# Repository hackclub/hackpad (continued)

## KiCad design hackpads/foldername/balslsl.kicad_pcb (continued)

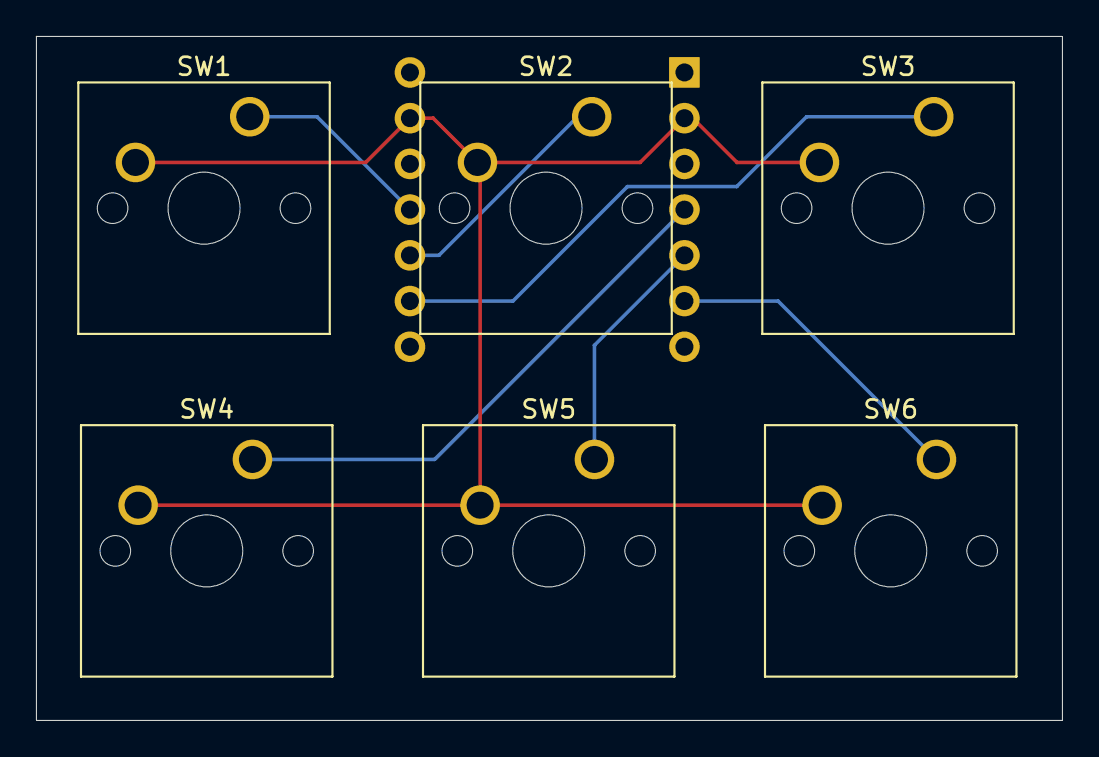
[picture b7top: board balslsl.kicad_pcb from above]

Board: 2 copper layers, 57.0 x 38.0 mm, 7 parts (1 on the bottom side), 7 nets.

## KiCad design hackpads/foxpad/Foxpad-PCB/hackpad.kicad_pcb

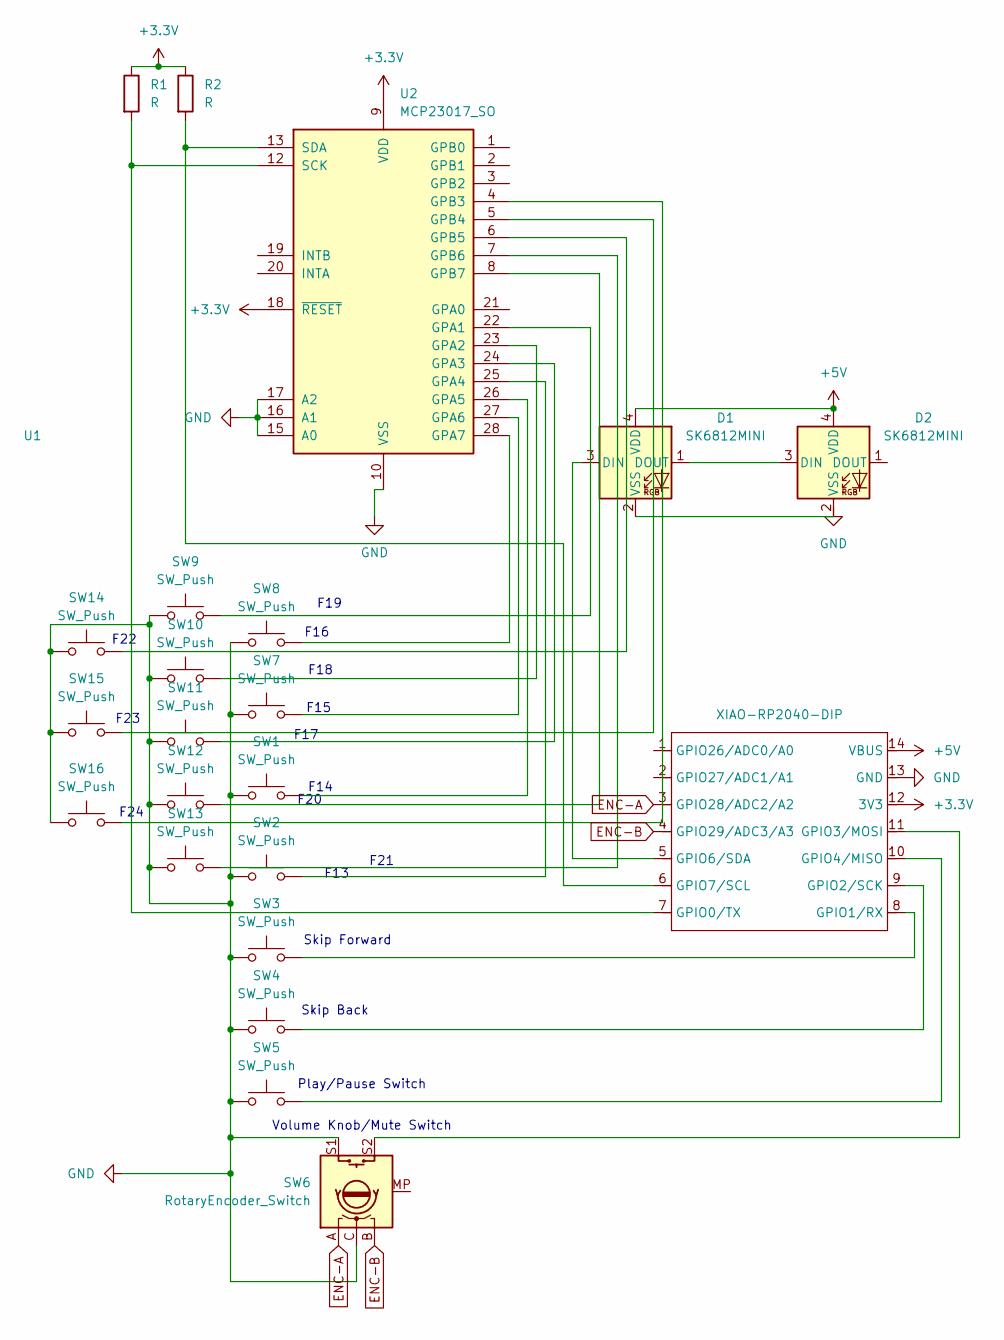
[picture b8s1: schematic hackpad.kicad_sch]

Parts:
D1, D2: SK6812MINI; LED_SK6812MINI_PLCC4_3.5x3.5mm_P1.75mm
R1, R2: R; R_Axial_DIN0204_L3.6mm_D1.6mm_P7.62mm_Horizontal
SW1, SW2, SW3, SW4, SW5, SW7, SW8, SW9, SW10, SW11, SW12, SW13, SW14, SW15, SW16: SW_Push; SW_Cherry_MX_1.00u_PCB
SW6: RotaryEncoder_Switch; RotaryEncoder_Alps_EC11E-Switch_Vertical_H20mm_CircularMoun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
U1: XIAO-RP2040-DIP
U2: MCP23017_SO; SOIC-28W_7.5x17.9mm_P1.27mm

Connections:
+3.3V: R1.1, R2.1, U1.12 (3V3), U2.9 (VDD), U2.18 (~RESET)
+5V: D1.4 (VDD), D2.4 (VDD), U1.14 (VBUS)
ENC-A: SW6.A, U1.3 (GPIO28/ADC2/A2)
ENC-B: SW6.B, U1.4 (GPIO29/ADC3/A3)
GND: SW1.1, SW2.1, SW3.1, SW4.1, SW5.1, SW6.C, SW6.S1, SW7.1, SW8.1, SW9.1, SW10.1, SW11.1, SW12.1, SW13.1, SW14.1, SW15.1, SW16.1, U1.13 (GND), U2.10 (VSS), U2.15 (A0), U2.16 (A1), U2.17 (A2)
unnamed: D1.3 (DIN), U1.5 (GPIO6/SDA)
unnamed: D1.1 (DOUT), D2.3 (DIN)
unnamed: D1.2 (VSS), D2.2 (VSS)
unnamed: R1.2, U1.7 (GPIO0/TX), U2.12 (SCK)
unnamed: SW3.2, U1.8 (GPIO1/RX)
unnamed: SW4.2, U1.9 (GPIO2/SCK)
unnamed: SW6.S2, U1.11 (GPIO3/MOSI)
unnamed: SW5.2, U1.10 (GPIO4/MISO)
unnamed: R2.2, U1.6 (GPIO7/SCL), U2.13 (SDA)
unnamed: SW9.2, U2.22 (GPA1)
unnamed: SW10.2, U2.23 (GPA2)
unnamed: SW11.2, U2.24 (GPA3)
unnamed: SW2.2, U2.25 (GPA4)
unnamed: SW1.2, U2.26 (GPA5)
unnamed: SW7.2, U2.27 (GPA6)
unnamed: SW8.2, U2.28 (GPA7)
unnamed: SW16.2, U2.4 (GPB3)
unnamed: SW15.2, U2.5 (GPB4)
unnamed: SW14.2, U2.6 (GPB5)
unnamed: SW13.2, U2.7 (GPB6)
unnamed: SW12.2, U2.8 (GPB7)

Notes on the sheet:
F16
F18
F13
F17
F23
Volume Knob/Mute Switch
F19
Skip Forward
F20
F22
F24
F15
Skip Back
F21
Play/Pause Switch
F14

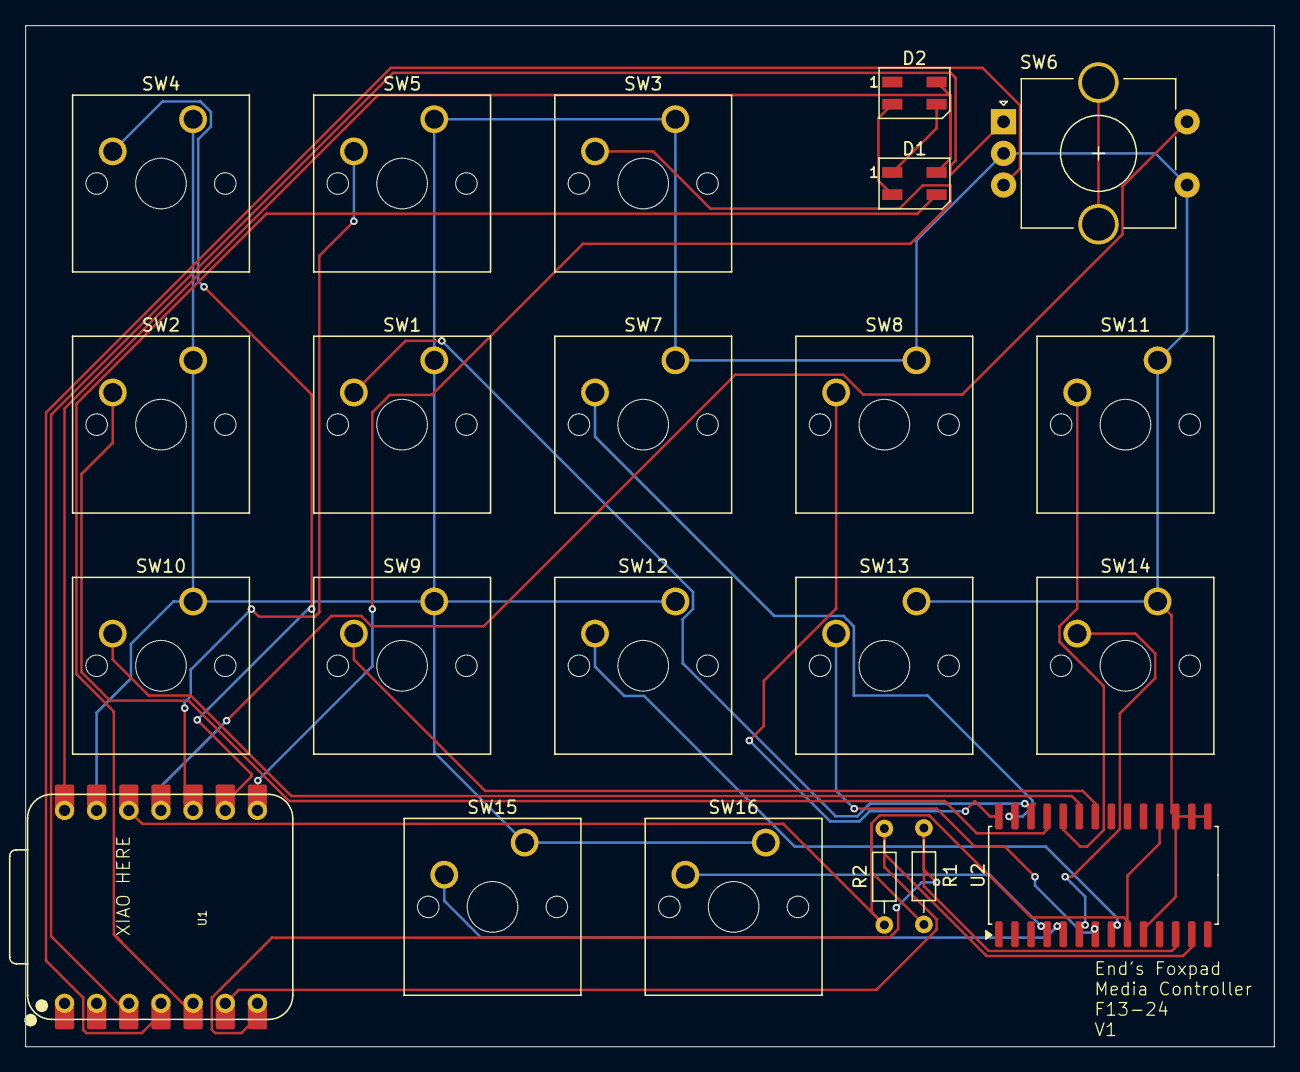
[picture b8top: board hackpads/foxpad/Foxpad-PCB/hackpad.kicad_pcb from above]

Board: 2 copper layers, 98.7 x 80.7 mm, 22 parts (0 on the bottom side), 26 nets.
